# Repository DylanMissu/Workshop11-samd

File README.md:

# LoRaWAN Logger ZERO+
| Front | Back |
|---|---|
| |  |

## Description
This board was made to help automate steam train management in an NPO. It is used to send status signals to a central server through LoRaWAN so the workers don’t have to go on site and check the states. There will also be an expansion board with relays to switch certain peripherals remotely.
It is equipped with 6 individual 24v tolerant isolated digital inputs. It can also be powered by 24v DC because it uses a buck converter to step the voltage down to 3.3v
Here are some other specifications:
* Microcontroller: ATSAMD21J18
* Flash: 256KB
* SRAM: 64KB
* Frequency: 48MHz
* ADC: 20-Channel 12bit
* DAC: Single-Channel 10bit 
* Pins: 52 GPIO pins

## This repository contains
* installation guide
* usage guide
* PCB and schematic files
* bootloader code and binaries
* ArduinoCore-samd libraries

## Installation
First open the configuration editor in Arduino under "File -> Preferences"
Then next to "Additional Boards Manager URLs" add the following url:
```
https://raw.githubusercontent.com/dylanmsu/Workshop11-samd/master/Workshop11Core-samd/package_workshop11_index.json
```

For a more detailed explanation, refer to [this guide](https://support.arduino.cc/hc/en-us/articles/360016119519-How-to-add-boards-in-the-board-manager).

## Usage
TODO

## Schematic
TODO

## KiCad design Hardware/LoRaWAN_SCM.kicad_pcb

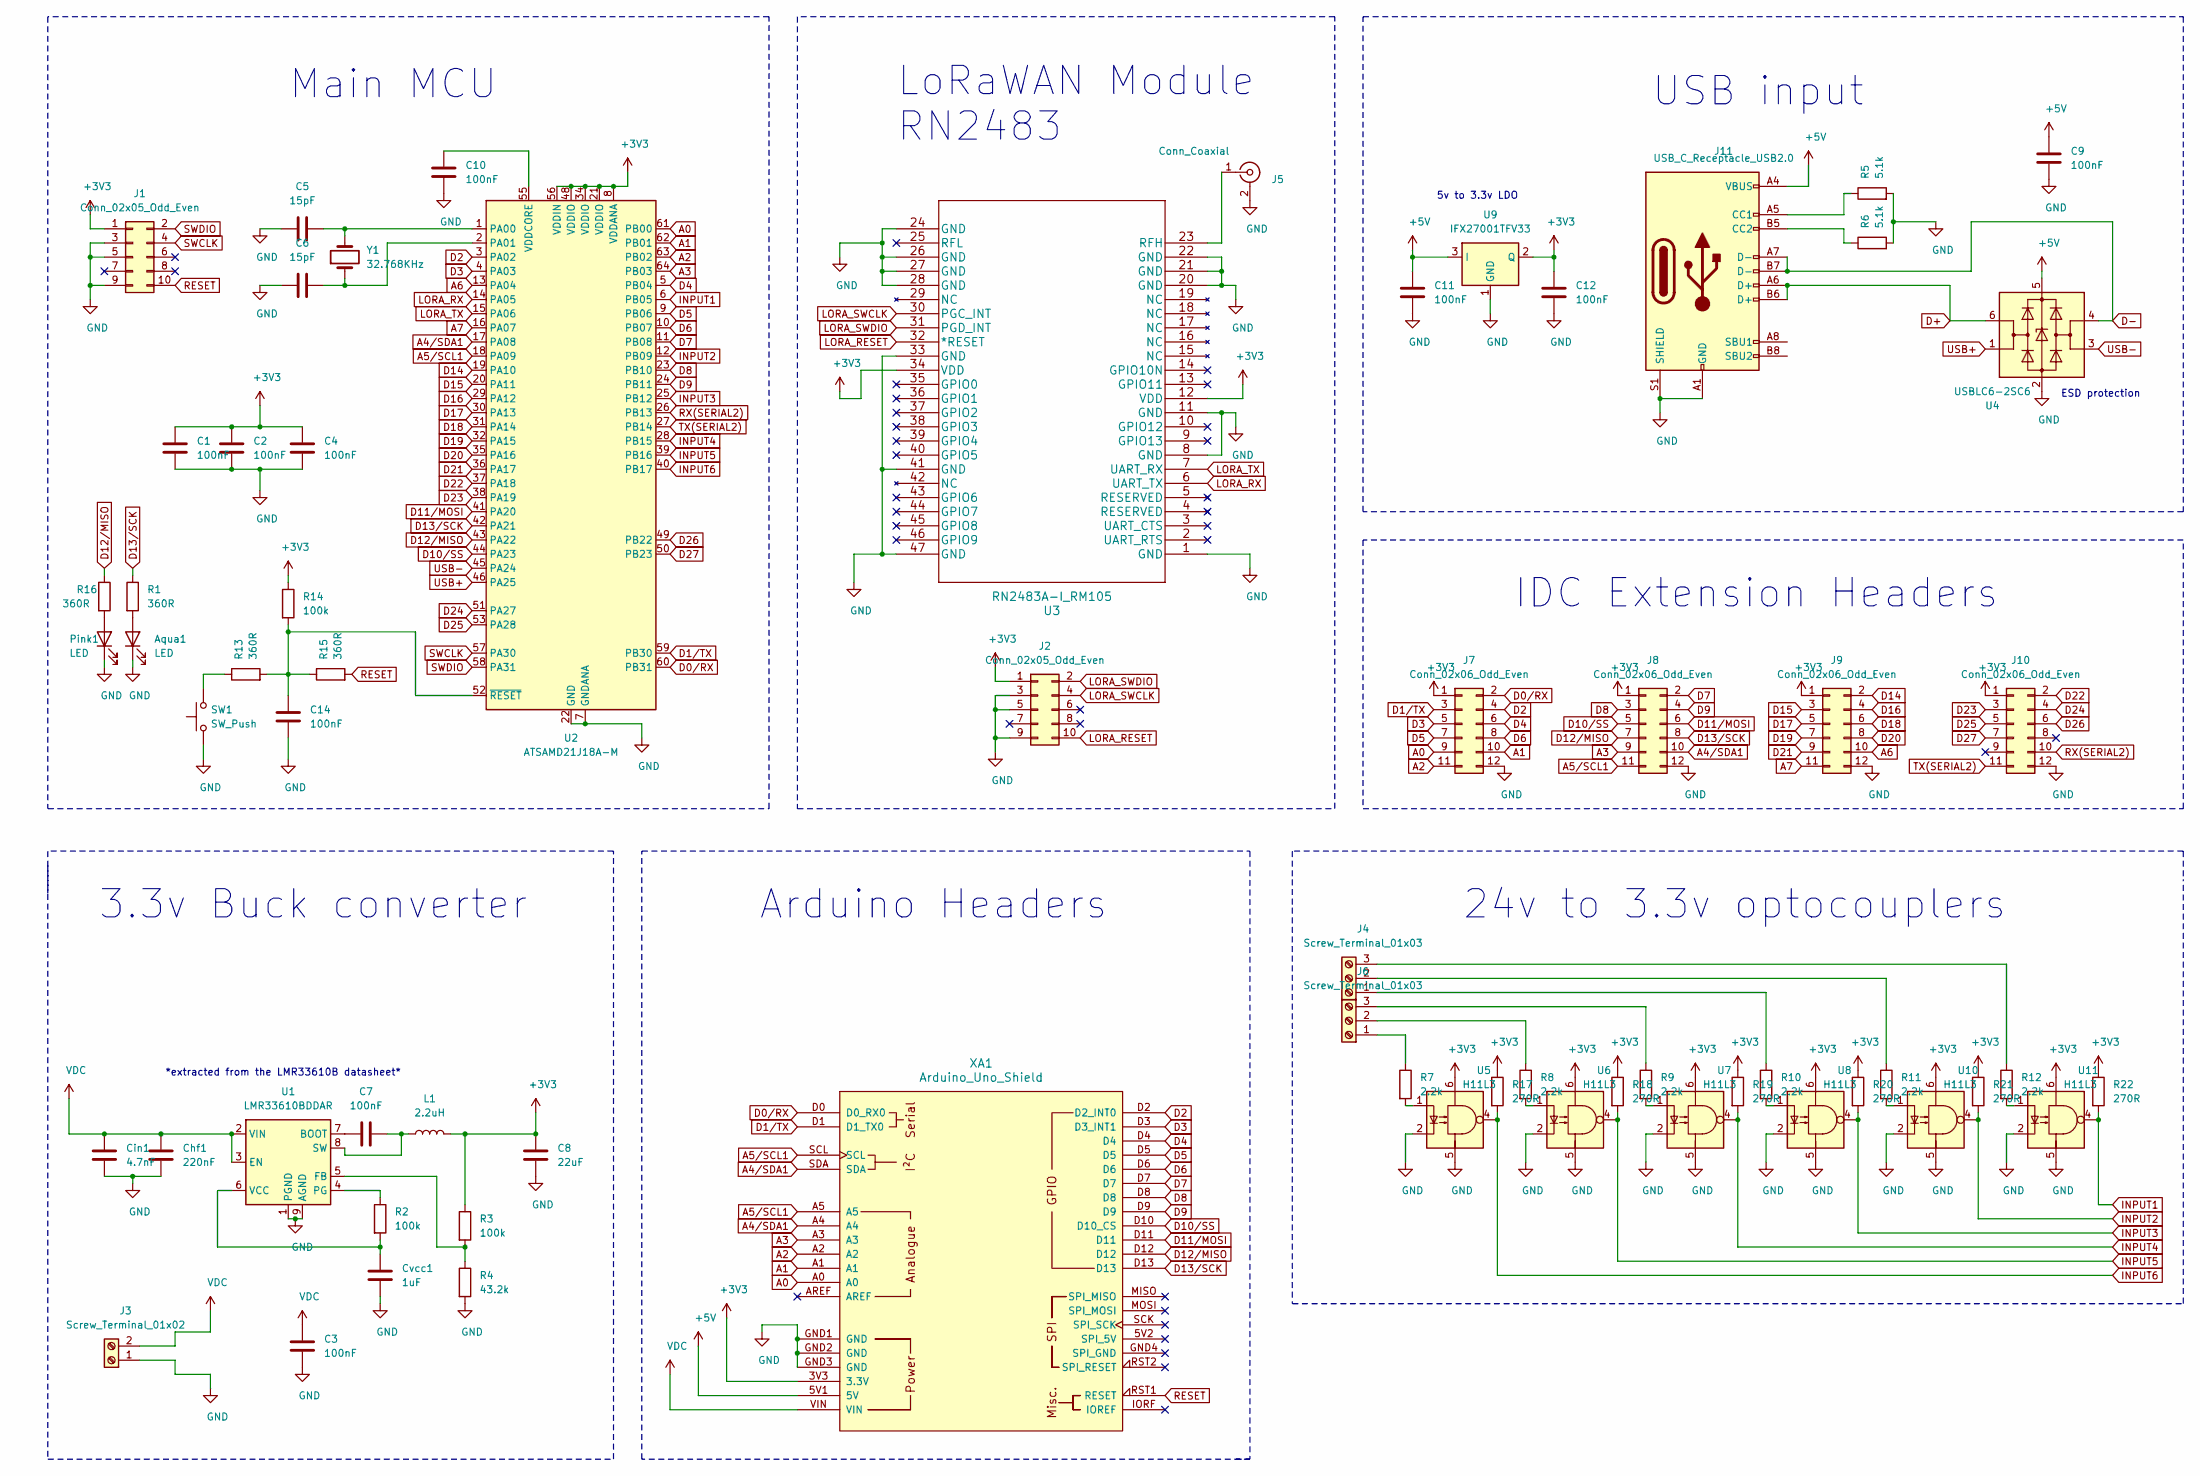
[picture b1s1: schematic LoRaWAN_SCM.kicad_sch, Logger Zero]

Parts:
Aqua1: LED; LED_0603_1608Metric_Pad1.05x0.95mm_HandSolder
C1, C2, C3, C4, C7, C9, C10, C11, C12, C14: 100nF; C_0805_2012Metric_Pad1.18x1.45mm_HandSolder
C5, C6: 15pF; C_0805_2012Metric_Pad1.18x1.45mm_HandSolder
C8: 22uF; CP_Elec_8x6.9
Chf1: 220nF; C_0805_2012Metric_Pad1.18x1.45mm_HandSolder
Cin1: 4.7nF; C_0805_2012Metric_Pad1.18x1.45mm_HandSolder
Cvcc1: 1uF; C_0805_2012Metric_Pad1.18x1.45mm_HandSolder
J1, J2: Conn_02x05_Odd_Even; PinHeader_2x05_P1.27mm_Vertical_SMD
J3: Screw_Terminal_01x02; TerminalBlock_bornier-2_P5.08mm
J4, J6: Screw_Terminal_01x03; TerminalBlock_bornier-3_P5.08mm
J5: Conn_Coaxial; SMA_Amphenol_132289_EdgeMount
J7, J8, J9, J10: Conn_02x06_Odd_Even; PinHeader_2x06_P2.54mm_Vertical
J11: USB_C_Receptacle_USB2.0
L1: 2.2uH; L_Taiyo-Yuden_NR-50xx_HandSoldering
Pink1: LED; LED_0603_1608Metric_Pad1.05x0.95mm_HandSolder
R1, R13, R15, R16: 360R; R_0805_2012Metric_Pad1.20x1.40mm_HandSolder
R2, R3, R14: 100k; R_0805_2012Metric_Pad1.20x1.40mm_HandSolder
R4: 43.2k; R_0805_2012Metric_Pad1.20x1.40mm_HandSolder
R5, R6: 5.1k; R_0805_2012Metric_Pad1.20x1.40mm_HandSolder
R7, R8, R9, R10, R11, R12: 2.2k; R_0805_2012Metric_Pad1.20x1.40mm_HandSolder
R17, R18, R19, R20, R21, R22: 270R; R_0805_2012Metric_Pad1.20x1.40mm_HandSolder
SW1: SW_Push; SW_SPST_TL3342
U1: LMR33610BDDAR; Texas_HSOP-8-1EP_3.9x4.9mm_P1.27mm_ThermalVias
U2: ATSAMD21J18A-M; QFN-64-1EP_9x9mm_P0.5mm_EP4.7x4.7mm
U3: RN2483A-I_RM105; RN2483
U4: USBLC6-2SC6; SOT-23-6
U5, U6, U7, U8, U10, U11: H11L3; DIP-6_W8.89mm_SMDSocket_LongPads
U9: IFX27001TFV33; SOT-223-3_TabPin2
XA1: Arduino_Uno_Shield
Y1: 32.768KHz; Crystal_SMD_3215-2Pin_3.2x1.5mm

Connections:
+3V3: C1.1, C2.1, C4.1, C8.1, C12.1, J1.1, J2.1, J7.1, J8.1, J9.1, J10.1, L1.2, R3.1, R14.1, R17.1, R18.1, R19.1, R20.1, R21.1, R22.1, U2.8 (VDDANA), U2.21 (VDDIO), U2.34 (VDDIO), U2.48 (VDDIO), U2.56 (VDDIN), U3.12 (VDD), U3.34 (VDD), U5.6, U6.6, U7.6, U8.6, U9.2 (Q), U10.6, U11.6, XA1.3V3 (3.3V)
+5V: C9.1, C11.1, J11.A4 (VBUS), J11.A9 (VBUS), J11.B4 (VBUS), J11.B9 (VBUS), U4.5 (VBUS), U9.3 (I), XA1.5V1 (5V); also elsewhere on the board
A0: J7.9, U2.61 (PB00), XA1.A0
A1: J7.10, U2.62 (PB01), XA1.A1
A2: J7.11, U2.63 (PB02), XA1.A2
A3: J8.9, U2.64 (PB03), XA1.A3
A4/SDA1: J8.10, U2.17 (PA08), XA1.A4, XA1.SDA
A5/SCL1: J8.11, U2.18 (PA09), XA1.A5, XA1.SCL
A6: J9.10, U2.13 (PA04)
A7: J9.11, U2.16 (PA07)
D0/RX: J7.2, U2.60 (PB31), XA1.D0 (D0_RX0)
D1/TX: J7.3, U2.59 (PB30), XA1.D1 (D1_TX0)
D2: J7.4, U2.3 (PA02), XA1.D2 (D2_INT0)
D3: J7.5, U2.4 (PA03), XA1.D3 (D3_INT1)
D4: J7.6, U2.5 (PB04), XA1.D4
D5: J7.7, U2.9 (PB06), XA1.D5
D6: J7.8, U2.10 (PB07), XA1.D6
D7: J8.2, U2.11 (PB08), XA1.D7
D8: J8.3, U2.23 (PB10), XA1.D8
D9: J8.4, U2.24 (PB11), XA1.D9
D10/SS: J8.5, U2.44 (PA23), XA1.D10 (D10_CS)
D11/MOSI: J8.6, U2.41 (PA20), XA1.D11
D12/MISO: J8.7, R16.1, U2.43 (PA22), XA1.D12
D13/SCK: J8.8, R1.1, U2.42 (PA21), XA1.D13
D14: J9.2, U2.19 (PA10)
D15: J9.3, U2.20 (PA11)
D16: J9.4, U2.29 (PA12)
D17: J9.5, U2.30 (PA13)
D18: J9.6, U2.31 (PA14)
D19: J9.7, U2.32 (PA15)
D20: J9.8, U2.35 (PA16)
D21: J9.9, U2.36 (PA17)
D22: J10.2, U2.37 (PA18)
D23: J10.3, U2.38 (PA19)
D24: J10.4, U2.51 (PA27)
D25: J10.5, U2.53 (PA28)
D26: J10.6, U2.49 (PB22)
D27: J10.7, U2.50 (PB23)
D+: J11.A6 (D+), J11.B6 (D+), U4.6 (I/O1); also elsewhere on the board
D-: J11.A7 (D-), J11.B7 (D-), U4.4 (I/O2); also elsewhere on the board
GND: Aqua1.1 (K), C1.2, C2.2, C3.2, C4.2, C5.1, C6.1, C8.2, C9.2, C10.2, C11.2, C12.2, C14.2, Chf1.2, Cin1.2, Cvcc1.2, J1.3, J1.5, J1.9, J2.3, J2.5, J2.9, J3.1, J5.2 (Ext), J7.12, J8.12, J9.12, J10.12, J11.A1 (GND), J11.A12 (GND), J11.B1 (GND), J11.B12 (GND), J11.S1 (SHIELD), Pink1.1 (K), R4.2, R5.2, R6.2, SW1.1, U1.1 (PGND), U1.9 (AGND), U2.7 (GNDANA), U2.22 (GND), U2.33 (GND), U2.47 (GND), U2.54 (GND), U3.1 (GND), U3.8 (GND), U3.11 (GND), U3.20 (GND), U3.21 (GND), U3.22 (GND), U3.24 (GND), U3.26 (GND), U3.27 (GND), U3.28 (GND), U3.33 (GND), U3.41 (GND), U3.47 (GND), U4.2 (GND), U5.2, U5.5, U6.2, U6.5, U7.2, U7.5, U8.2, U8.5, U9.1 (GND), U10.2, U10.5, U11.2, U11.5, XA1.GND1 (GND), XA1.GND2 (GND), XA1.GND3 (GND); also elsewhere on the board
INPUT1: R22.2, U2.6 (PB05), U11.4
INPUT2: R21.2, U2.12 (PB09), U10.4
INPUT3: R20.2, U2.25 (PB12), U8.4
INPUT4: R19.2, U2.28 (PB15), U7.4
INPUT5: R18.2, U2.39 (PB16), U6.4
INPUT6: R17.2, U2.40 (PB17), U5.4
LORA_RESET: J2.10, U3.32 (*RESET)
LORA_RX: U2.14 (PA05), U3.6 (UART_TX)
LORA_SWCLK: J2.4, U3.30 (PGC_INT)
LORA_SWDIO: J2.2, U3.31 (PGD_INT)
LORA_TX: U2.15 (PA06), U3.7 (UART_RX)
unnamed: Aqua1.2 (A), R1.2
unnamed: C5.2, U2.1 (PA00), Y1.2
unnamed: C6.2, U2.2 (PA01), Y1.1
unnamed: C7.1, L1.1, U1.8 (SW)
unnamed: C7.2, U1.7 (BOOT)
unnamed: C10.1, U2.55 (VDDCORE)
unnamed: C14.1, R13.2, R14.2, R15.1, U2.52 (~RESET)
unnamed: Cvcc1.1, R2.2, U1.6 (VCC)
unnamed: J4.1, R10.1
unnamed: J4.2, R11.1
unnamed: J4.3, R12.1
unnamed: J5.1 (In), U3.23 (RFH)
unnamed: J6.1, R7.1
unnamed: J6.2, R8.1
unnamed: J6.3, R9.1
unnamed: Pink1.2 (A), R16.2
unnamed: R2.1, U1.4 (PG)
unnamed: R3.2, R4.1, U1.5 (FB)
unnamed: J11.A5 (CC1), R5.1
unnamed: J11.B5 (CC2), R6.1
unnamed: R7.2, U5.1
unnamed: R8.2, U6.1
unnamed: R9.2, U7.1
unnamed: R10.2, U8.1
unnamed: R11.2, U10.1
unnamed: R12.2, U11.1
unnamed: R13.1, SW1.2
RESET: J1.10, R15.2, XA1.RST1 (RESET)
RX(SERIAL2): J10.10, U2.26 (PB13)
SWCLK: J1.4, U2.57 (PA30)
SWDIO: J1.2, U2.58 (PA31)
TX(SERIAL2): J10.11, U2.27 (PB14)
USB+: U2.46 (PA25), U4.1 (I/O1)
USB-: U2.45 (PA24), U4.3 (I/O2)
VDC: C3.1, Chf1.1, Cin1.1, J3.2, U1.2 (VIN), U1.3 (EN), XA1.VIN

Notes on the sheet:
Main MCU
*extracted from the LMR33610B datasheet*
3.3v Buck converter
LoRaWAN Module RN2483
Arduino Headers
24v to 3.3v optocouplers
5v to 3.3v LDO
USB input
IDC Extension Headers
ESD protection

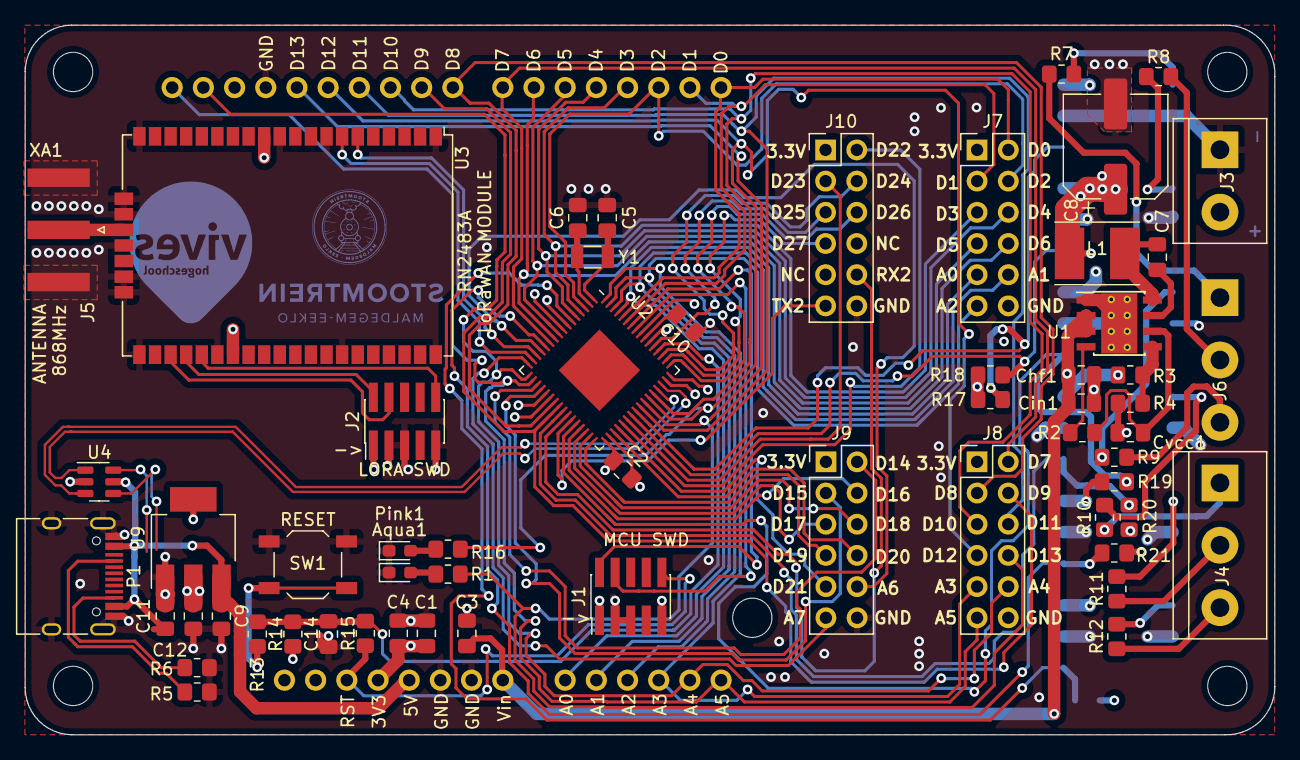
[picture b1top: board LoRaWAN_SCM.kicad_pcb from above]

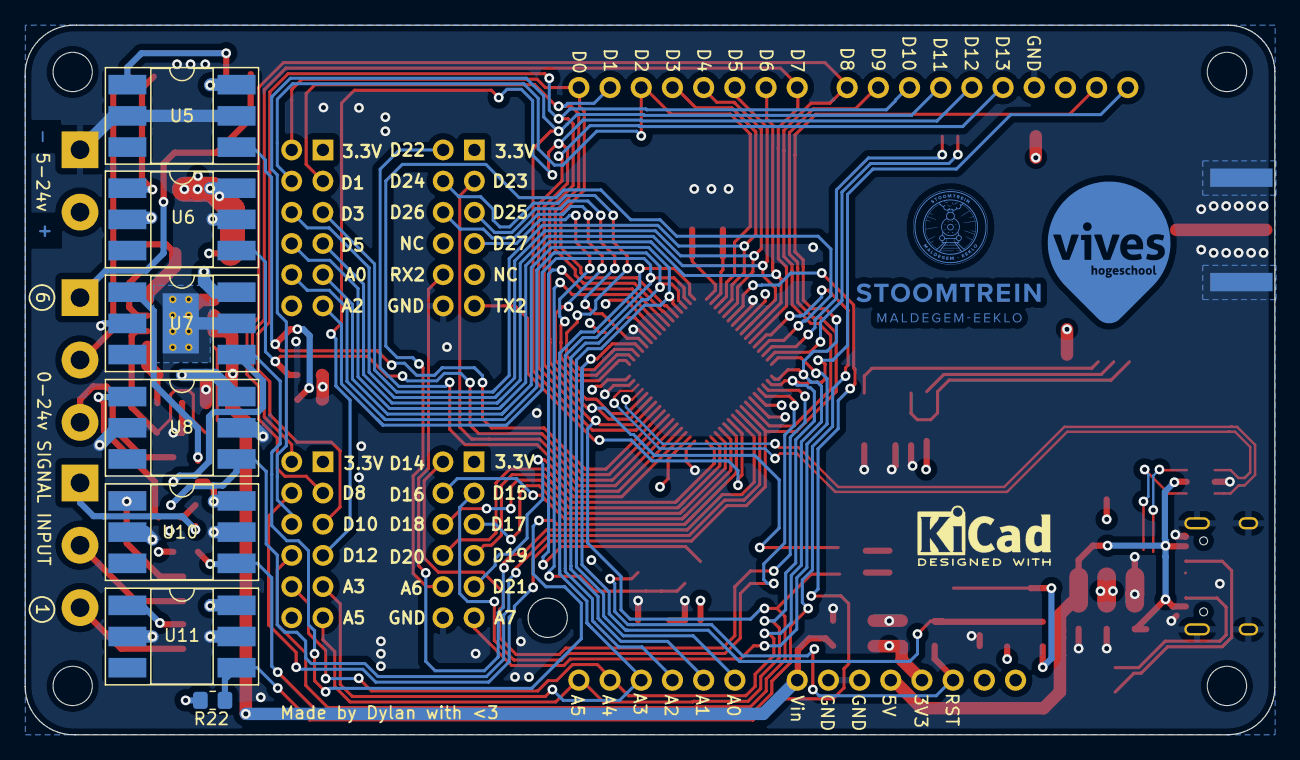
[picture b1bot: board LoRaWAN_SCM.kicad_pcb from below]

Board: 4 copper layers, 101.8 x 57.8 mm, 66 parts (7 on the bottom side), 85 nets.

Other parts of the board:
P1: USB_C_Plug_USB2.0; USB_C_Receptacle_HRO_TYPE-C-31-M-12

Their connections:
+5V: P1.A4 (VBUS), P1.A9 (VBUS), P1.B4 (VBUS), P1.B9 (VBUS); also elsewhere on the board
D+: P1.A6 (D+); also elsewhere on the board
D-: P1.A7 (D-); also elsewhere on the board
GND: P1.A1 (GND), P1.A12 (GND), P1.B1 (GND), P1.B12 (GND), P1.S1 (SHIELD); also elsewhere on the board

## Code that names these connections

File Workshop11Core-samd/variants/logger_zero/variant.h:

/*
  Copyright (c) 2014-2015 Arduino LLC.  All right reserved.

  This library is free software; you can redistribute it and/or
  modify it under the terms of the GNU Lesser General Public
  License as published by the Free Software Foundation; either
  version 2.1 of the License, or (at your option) any later version.

  This library is distributed in the hope that it will be useful,
  but WITHOUT ANY WARRANTY; without even the implied warranty of
  MERCHANTABILITY or FITNESS FOR A PARTICULAR PURPOSE.
  See the GNU Lesser General Public License for more details.

  You should have received a copy of the GNU Lesser General Public
  License along with this library; if not, write to the Free Software
  Foundation, Inc., 51 Franklin St, Fifth Floor, Boston, MA  02110-1301  USA
*/

#ifndef _VARIANT_SODAQ_EXPLORER_
#define _VARIANT_SODAQ_EXPLORER_

// The definitions here needs a SAMD core >=1.6.10
#define ARDUINO_SAMD_VARIANT_COMPLIANCE 10610

/*----------------------------------------------------------------------------
 *        Definitions
 *----------------------------------------------------------------------------*/

/** Frequency of the board main oscillator */
#define VARIANT_MAINOSC       (32768ul)

/** Master clock frequency */
#define VARIANT_MCK           (48000000ul)

/** Copied from bootloader. It will cause a "stay in bootloader" when doing 1200bps-touch */
#define BOOT_DOUBLE_TAP_ADDRESS         (0x20007FFCul)
#define BOOT_DOUBLE_TAP_DATA            (*((volatile uint32_t *) BOOT_DOUBLE_TAP_ADDRESS))
#define DOUBLE_TAP_MAGIC                0x07738135

/*----------------------------------------------------------------------------
 *        Headers
 *----------------------------------------------------------------------------*/

#include "WVariant.h"

#ifdef __cplusplus
#include "SERCOM.h"
#include "Uart.h"
#endif // __cplusplus

#ifdef __cplusplus
extern "C"
{
#endif // __cplusplus

/*----------------------------------------------------------------------------
 *        Pins
 *----------------------------------------------------------------------------*/

// Number of pins defined in PinDescription array
#define PINS_COUNT           (49u)
#define NUM_DIGITAL_PINS     (20u)
#define NUM_ANALOG_INPUTS    (9u)
#define NUM_ANALOG_OUTPUTS   (1u)

#define digitalPinToPort(P)        ( &(PORT->Group[g_APinDescription[P].ulPort]) )
#define digitalPinToBitMask(P)     ( 1 << g_APinDescription[P].ulPin )
//#define analogInPinToBit(P)        ( )
#define portOutputRegister(port)   ( &(port->OUT.reg) )
#define portInputRegister(port)    ( &(port->IN.reg) )
#define portModeRegister(port)     ( &(port->DIR.reg) )
#define digitalPinHasPWM(P)        ( g_APinDescription[P].ulPWMChannel != NOT_ON_PWM || g_APinDescription[P].ulTCChannel != NOT_ON_TIMER )

/*
 * digitalPinToTimer(..) is AVR-specific and is not defined for SAMD
 * architecture. If you need to check if a pin supports PWM you must
 * use digitalPinHasPWM(..).
 *
 * https://github.com/arduino/Arduino/issues/1833
 */
// #define digitalPinToTimer(P)

// LEDs
#define LED_BLUE            (12u)
#define PIN_LED             LED_BLUE
#define LED_BUILTIN         LED_BLUE

#define LED_PINK            (13u)

// RESET LINES
#define LORA_RESET          (45u)

/*
 * Analog pins
 */
#define PIN_A0               (30ul)
#define PIN_A1               (PIN_A0 + 1)
#define PIN_A2               (PIN_A0 + 2)
#define PIN_A3               (PIN_A0 + 3)
#define PIN_A4               (PIN_A0 + 4)
#define PIN_A5               (PIN_A0 + 5)
#define PIN_A6               (PIN_A0 + 6)
#define PIN_A7               (PIN_A0 + 7)

#define PIN_INPUT1           (24ul)
#define PIN_INPUT2           (25ul)
#define PIN_INPUT3           (26ul)
#define PIN_INPUT4           (27ul)
#define PIN_INPUT5           (28ul)
#define PIN_INPUT6           (29ul)

static const uint8_t A0  = PIN_A0 ;
static const uint8_t A1  = PIN_A1 ;
static const uint8_t A2  = PIN_A2 ;
static const uint8_t A3  = PIN_A3 ;
static const uint8_t A4  = PIN_A4 ;
static const uint8_t A5  = PIN_A5 ;
static const uint8_t A6  = PIN_A6 ;
static const uint8_t A7  = PIN_A7 ;


static const uint8_t INPUT1  = PIN_INPUT1 ;
static const uint8_t INPUT2  = PIN_INPUT2 ;
static const uint8_t INPUT3  = PIN_INPUT3 ;
static const uint8_t INPUT4  = PIN_INPUT4 ;
static const uint8_t INPUT5  = PIN_INPUT5 ;
static const uint8_t INPUT6  = PIN_INPUT6 ;

#define ADC_RESOLUTION      12


static const uint8_t DAC0 = 43u ; // or (35u) implications for cores/arduino/wiring_analog.c analogWrite()


/*
 * Serial interfaces
 */
// Serial
#define PIN_SERIAL_RX       (0ul)
#define PIN_SERIAL_TX       (1ul)
#define PAD_SERIAL_TX       (UART_TX_PAD_0)
#define PAD_SERIAL_RX       (SERCOM_RX_PAD_1)

// Serial1
#define PIN_SERIAL1_RX       (30ul)
#define PIN_SERIAL1_TX       (29ul)
#define PAD_SERIAL1_TX       (UART_TX_PAD_2)
#define PAD_SERIAL1_RX       (SERCOM_RX_PAD_1)

// Serial2
#define PIN_SERIAL2_RX       (40ul)
#define PIN_SERIAL2_TX       (41ul)
#define PAD_SERIAL2_TX       (UART_TX_PAD_2)
#define PAD_SERIAL2_RX       (SERCOM_RX_PAD_1)

/*
 * SPI Interfaces
 */


#define SPI_INTERFACES_COUNT 1

// SPI
#define PIN_SPI_MISO         (37u)
#define PIN_SPI_SS           (38u)
#define PIN_SPI_MOSI         (39u)
#define PIN_SPI_SCK          (40u)

static const uint8_t MISO = PIN_SPI_MISO;
static const uint8_t SS   = PIN_SPI_SS ;
static const uint8_t SS_DFLASH  = 44 ;
static const uint8_t MOSI = PIN_SPI_MOSI ;
static const uint8_t SCK  = PIN_SPI_SCK ;


/*
 * Wire Interfaces
 */
#define WIRE_INTERFACES_COUNT 2

#define PIN_WIRE_SDA         (33u)
#define PIN_WIRE_SCL         (34u)

#define PIN_WIRE1_SDA        (35u)
#define PIN_WIRE1_SCL        (36u)


/*
 * USB
 */
#define PIN_USB_DM          (42ul)
#define PIN_USB_DP          (43ul)

#ifdef __cplusplus
}
#endif

/*----------------------------------------------------------------------------
 *        Arduino objects - C++ only
 *----------------------------------------------------------------------------*/

#ifdef __cplusplus

/*  =========================
 *  ===== SERCOM DEFINITION
 *  =========================
*/
extern SERCOM sercom0;
extern SERCOM sercom1;
extern SERCOM sercom2;
extern SERCOM sercom3;
extern SERCOM sercom4;
extern SERCOM sercom5;

extern Uart Serial;
extern Uart Serial1;
extern Uart Serial2;

#endif

// These serial port names are intended to allow libraries and architecture-neutral
// sketches to automatically default to the correct port name for a particular type
// of use.  For example, a GPS module would normally connect to SERIAL_PORT_HARDWARE_OPEN,
// the first hardware serial port whose RX/TX pins are not dedicated to another use.
//
// SERIAL_PORT_MONITOR        Port which normally prints to the Arduino Serial Monitor
//
// SERIAL_PORT_USBVIRTUAL     Port which is USB virtual serial
//
// SERIAL_PORT_LINUXBRIDGE    Port which connects to a Linux system via Bridge library
//
// SERIAL_PORT_HARDWARE       Hardware serial port, physical RX & TX pins.
//
// SERIAL_PORT_HARDWARE_OPEN  Hardware serial ports which are open for use.  Their RX & TX
//                            pins are NOT connected to anything by default.
#define SERIAL_PORT_USBVIRTUAL      SerialUSB
#define SERIAL_PORT_MONITOR         SerialUSB

// Serial has no physical pins broken out, so it's not listed as HARDWARE port
#define SERIAL_PORT_HARDWARE        Serial
#define SERIAL_PORT_HARDWARE_OPEN   Serial

#define SERIAL_PORT_HARDWARE1       Serial1
#define SERIAL_PORT_HARDWARE_OPEN1  Serial1

#define SERIAL_PORT_HARDWARE2       Serial2
#define SERIAL_PORT_HARDWARE_OPEN2  Serial2

#define PERIPH_WIRE                 sercom1
#define WIRE_IT_HANDLER             SERCOM1_Handler

#define PERIPH_WIRE1                sercom2
#define WIRE1_IT_HANDLER            SERCOM2_Handler

#define PERIPH_SPI                  sercom3
#define PAD_SPI_TX                  SPI_PAD_2_SCK_3
#define PAD_SPI_RX                  SERCOM_RX_PAD_0


#endif /* _VARIANT_SODAQ_EXPLORER */

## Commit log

2021-02-18 added bootloader for custom development board
2021-02-18 added first board variant
2021-02-18 updated package json
2021-02-19 got lib to compile succesfully
2021-03-12 removed unused files
2021-03-12 updated files and included kicad project
2021-03-12 added images of the pcb
2021-03-12 Create LICENSE
2021-03-15 updated bootloader and variants
2021-04-02 updated arduino code and fixed usb isuue on pcb
